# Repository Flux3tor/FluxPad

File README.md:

# FluxPad

FluxPad is a custom 12-key macropad powered by the Seeed XIAO RP2040.  
It features a rotary encoder for volume and scrolling, an OLED status display, and a compact 3D-printed case designed for daily productivity and creative workflows.

---

## Features
- 12 MX mechanical keys
- Rotary encoder (volume + scroll control)
- 0.91" OLED display (layer & status display)
- Seeed XIAO RP2040 microcontroller
- QMK firmware
- Fully custom 2-layer PCB
- 3D-printed case

---

## Project Images

### Schematic

### PCB

### Case Design
#### Bottom Case

#### Top Case

### Final Layout

---

## System Overview

### MCU
- Seeed Studio XIAO RP2040 (Through-hole)

### Inputs
- 12x MX mechanical switches
- 1x EC11 rotary encoder

### Output
- 0.91" OLED display (I2C)

---

## Pin Mapping

| Function | GPIO |
|----------|------|
| ROW0 | GPIO26 |
| ROW1 | GPIO27 |
| ROW2 | GPIO28 |
| COL0 | GPIO29 |
| COL1 | GPIO0 |
| COL2 | GPIO1 |
| COL3 | GPIO2 |
| Encoder A | GPIO4 |
| Encoder B | GPIO3 |
| OLED SDA | GPIO6 |
| OLED SCL | GPIO7 |

---

## Bill of Materials (BOM)

| Part | Quantity | Manufacturer | Part Number |
|------|----------|--------------|-------------|
| Seeed XIAO RP2040 (TH) | 1 | Seeed Studio | 102010428 |
| MX Mechanical Switch | 12 | Gateron / Kailh | MX-Style |
| 1N4148 Diodes (TH) | 12 | Vishay | 1N4148 |
| EC11 Rotary Encoder | 1 | ALPS / Generic | EC11 |
| 0.91" OLED Display | 1 | Generic | SSD1306 |
| DSA Keycaps | 12 | Generic | DSA Blank |
| M3x16 Screws | 4 | Generic | M3 |
| Heatset Inserts | 4 | Generic | M3 |

---

## Firmware
FluxPad runs on QMK.  
The firmware supports:
- Key matrix scanning
- OLED display support

Source code is located in the `Firmware/` folder.

---

## Case
The case is fully 3D printed and designed in Fusion360.  
It consists of:
- Bottom shell
- Top plate
- Heatset insert mounts

Exported as three STEP files in the `CAD/` folder.

---

## Build Process

This was my first time soldering, and I ran into a few issues along the way.

While soldering the XIAO RP2040 headers, I accidentally bent the pins without realizing. Instead of redoing everything, I fixed it by using ribbon wires to connect the headers to the PCB. It doesn't look perfect, but it works reliably.

Soldering the full PCB took around 5 hours.

### Firmware Issues

Initially, I used KMK firmware, but it kept crashing when I added OLED support. To debug, I tested the OLED separately using Arduino IDE and confirmed it was working.

I then switched to QMK and rewrote the firmware from scratch, which took another ~5 hours. After that, everything worked properly, including the OLED and encoder.

---

## Final Build

---

## Demo Video

[Watch FluxPad Demo](https://drive.google.com/file/d/1hNpVQt3ci1zXDI4beTaH4Mk9EOGyLXIW/view?usp=drive_link)

---

## Result

The final FluxPad works as intended:
- All 12 keys function correctly  
- Rotary encoder works for control  
- OLED display works  

It may not look perfect due to manual fixes, but it is fully functional and used daily.

---

## Author
Designed and built by **Flux3tor**  
Hack Club Hackpad Project

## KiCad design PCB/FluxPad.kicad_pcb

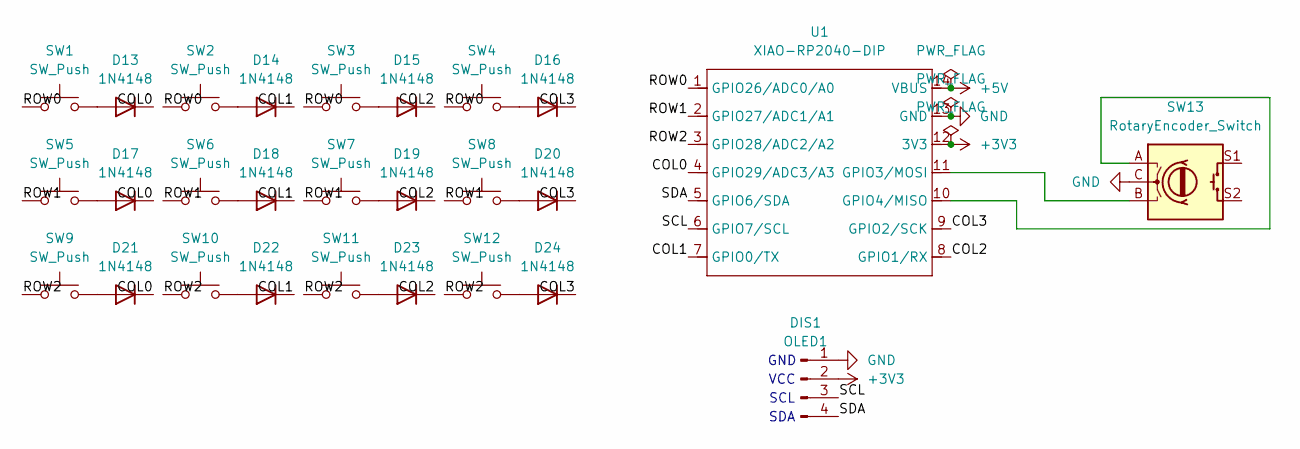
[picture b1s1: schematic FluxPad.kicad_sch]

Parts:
D13, D14, D15, D16, D17, D18, D19, D20, D21, D22, D23, D24: 1N4148; D_DO-35_SOD27_P7.62mm_Horizontal
DIS1: OLED1; SSD1306-0.91-OLED-4pin-128x32
SW1, SW2, SW3, SW4, SW5, SW6, SW7, SW8, SW9, SW10, SW11, SW12: SW_Push; SW_Cherry_MX_1.00u_PCB
SW13: RotaryEncoder_Switch; RotaryEncoder_Alps_EC11E-Switch_Vertical_H20mm
U1: XIAO-RP2040-DIP

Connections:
+3V3: DIS1.2, U1.12 (3V3)
+5V: U1.14 (VBUS)
/COL0: D13.1 (K), D17.1 (K), D21.1 (K), U1.4 (GPIO29/ADC3/A3)
/COL1: D14.1 (K), D18.1 (K), D22.1 (K), U1.7 (GPIO0/TX)
/COL2: D15.1 (K), D19.1 (K), D23.1 (K), U1.8 (GPIO1/RX)
/COL3: D16.1 (K), D20.1 (K), D24.1 (K), U1.9 (GPIO2/SCK)
/ROW0: SW1.1, SW2.1, SW3.1, SW4.1, U1.1 (GPIO26/ADC0/A0)
/ROW1: SW5.1, SW6.1, SW7.1, SW8.1, U1.2 (GPIO27/ADC1/A1)
/ROW2: SW9.1, SW10.1, SW11.1, SW12.1, U1.3 (GPIO28/ADC2/A2)
/SCL: DIS1.3, U1.6 (GPIO7/SCL)
/SDA: DIS1.4, U1.5 (GPIO6/SDA)
GND: DIS1.1, SW13.C, U1.13 (GND)
unnamed: D13.2 (A), SW1.2
unnamed: D14.2 (A), SW2.2
unnamed: D15.2 (A), SW3.2
unnamed: D16.2 (A), SW4.2
unnamed: D17.2 (A), SW5.2
unnamed: D18.2 (A), SW6.2
unnamed: D19.2 (A), SW7.2
unnamed: D20.2 (A), SW8.2
unnamed: D21.2 (A), SW9.2
unnamed: D22.2 (A), SW10.2
unnamed: D23.2 (A), SW11.2
unnamed: D24.2 (A), SW12.2
unnamed: SW13.B, U1.11 (GPIO3/MOSI)
unnamed: SW13.A, U1.10 (GPIO4/MISO)

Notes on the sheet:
GND
SDA
SCL
VCC

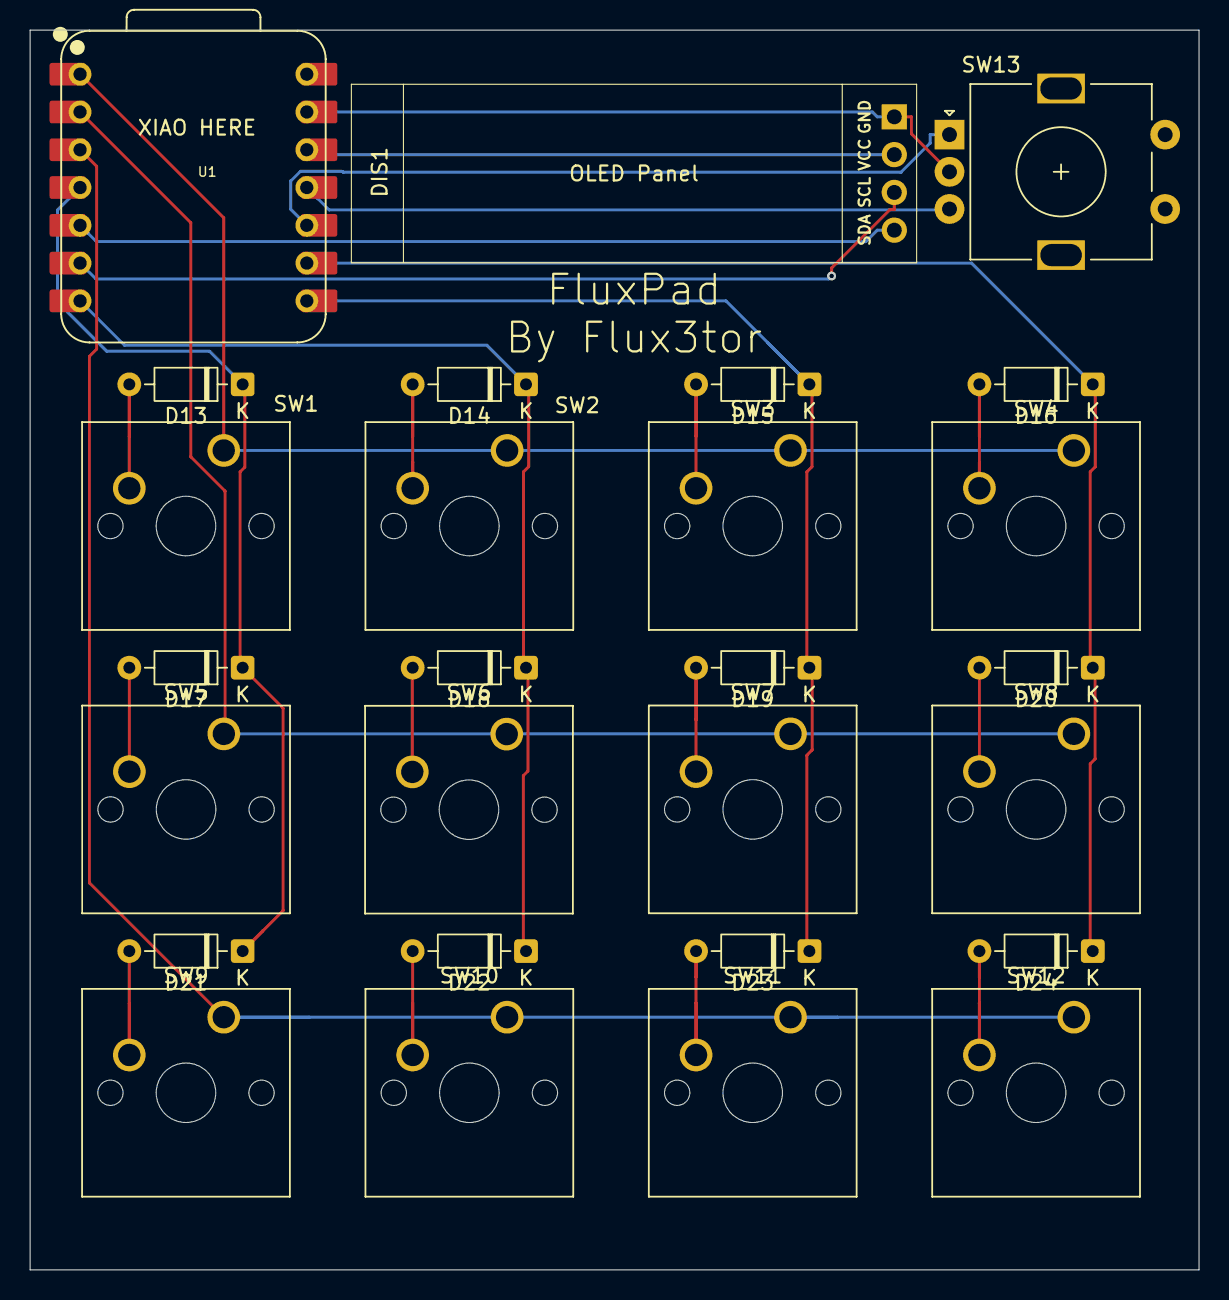
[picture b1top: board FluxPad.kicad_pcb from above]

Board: 2 copper layers, 78.6 x 83.3 mm, 27 parts (0 on the bottom side), 25 nets.

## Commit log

2026-01-24 Updated README and added images
2026-01-25 Fixed Some Misalignments
2026-01-25 Updated The Images
2026-01-27 Added Gerber Files
2026-02-25 Switched to QMK because KMK doesnt like me
